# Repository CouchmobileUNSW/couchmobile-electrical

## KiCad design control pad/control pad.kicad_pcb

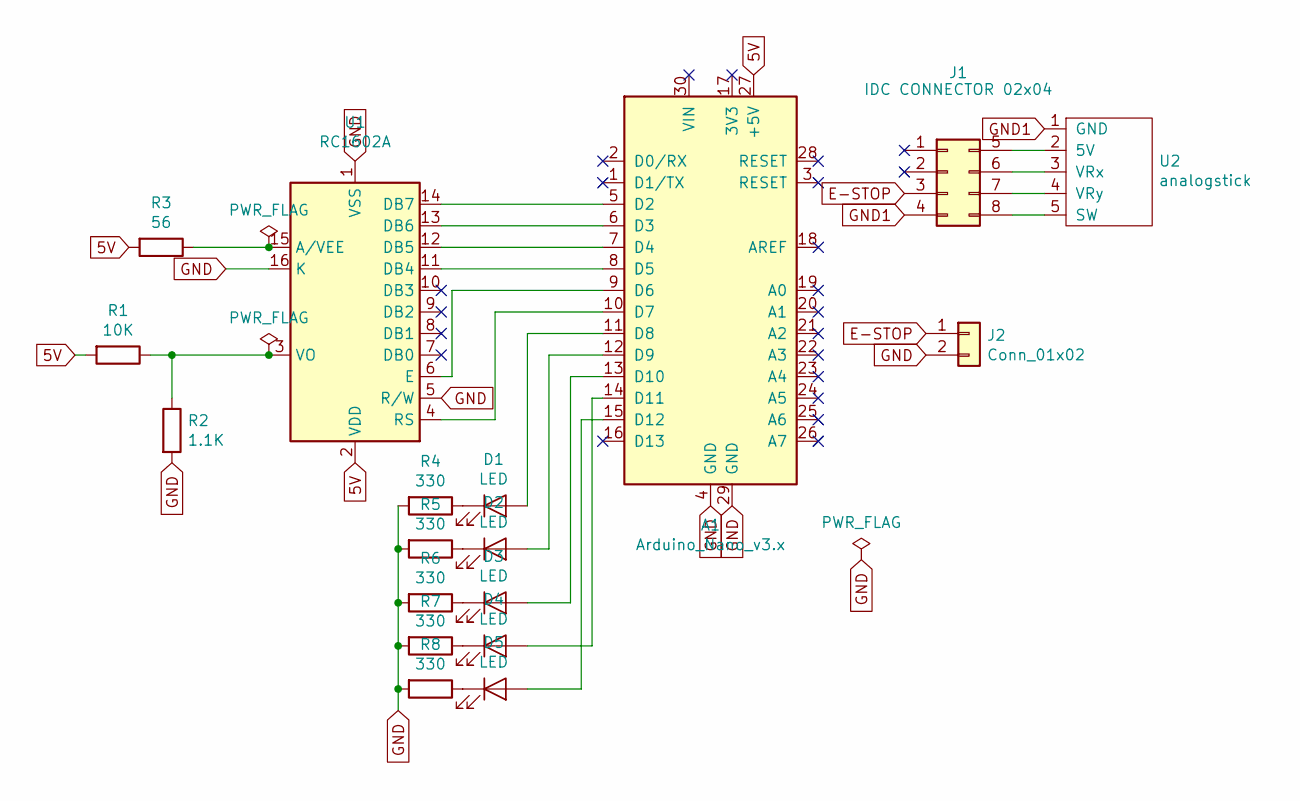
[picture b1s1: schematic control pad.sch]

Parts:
A1: Arduino_Nano_v3.x; Arduino_Nano_WithMountingHoles
D1, D2, D3, D4, D5: LED; D_0805_2012Metric_Pad1.15x1.40mm_HandSolder
J1: IDC CONNECTOR 02x04; IDC-Header_2x04_P2.54mm_Vertical
J2: Conn_01x02; PinHeader_1x02_P2.54mm_Vertical
R1: 10K; R_0805_2012Metric_Pad1.15x1.40mm_HandSolder
R2: 1.1K; R_0805_2012Metric_Pad1.15x1.40mm_HandSolder
R3: 56; R_0805_2012Metric_Pad1.15x1.40mm_HandSolder
R4, R5, R6, R7, R8: 330; R_0805_2012Metric_Pad1.15x1.40mm_HandSolder
U1: RC1602A; WC1602A
U2: analogstick; PinHeader_1x05_P2.54mm_Vertical

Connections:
5V: A1.27 (+5V), R1.2, R3.2, U1.2 (VDD)
E-STOP: J1.3, J2.1
GND: A1.4 (GND), A1.29 (GND), J2.2, R2.2, R4.2, R5.2, R6.2, R7.2, R8.2, U1.1 (VSS), U1.5 (R/W), U1.16 (K)
GND1: J1.4, U2.1 (GND)
unnamed: A1.5 (D2), U1.14 (DB7)
unnamed: A1.6 (D3), U1.13 (DB6)
unnamed: A1.7 (D4), U1.12 (DB5)
unnamed: A1.8 (D5), U1.11 (DB4)
unnamed: A1.9 (D6), U1.6 (E)
unnamed: A1.10 (D7), U1.4 (RS)
unnamed: A1.11 (D8), D1.2 (A)
unnamed: A1.12 (D9), D2.2 (A)
unnamed: A1.13 (D10), D3.2 (A)
unnamed: A1.14 (D11), D4.2 (A)
unnamed: A1.15 (D12), D5.2 (A)
unnamed: D1.1 (K), R4.1
unnamed: D2.1 (K), R5.1
unnamed: D3.1 (K), R6.1
unnamed: D4.1 (K), R7.1
unnamed: D5.1 (K), R8.1
unnamed: J1.5, U2.2 (5V)
unnamed: J1.6, U2.3 (VRx)
unnamed: J1.7, U2.4 (VRy)
unnamed: J1.8, U2.5 (SW)
unnamed: R1.1, R2.1, U1.3 (VO)
unnamed: R3.1, U1.15 (A/VEE)

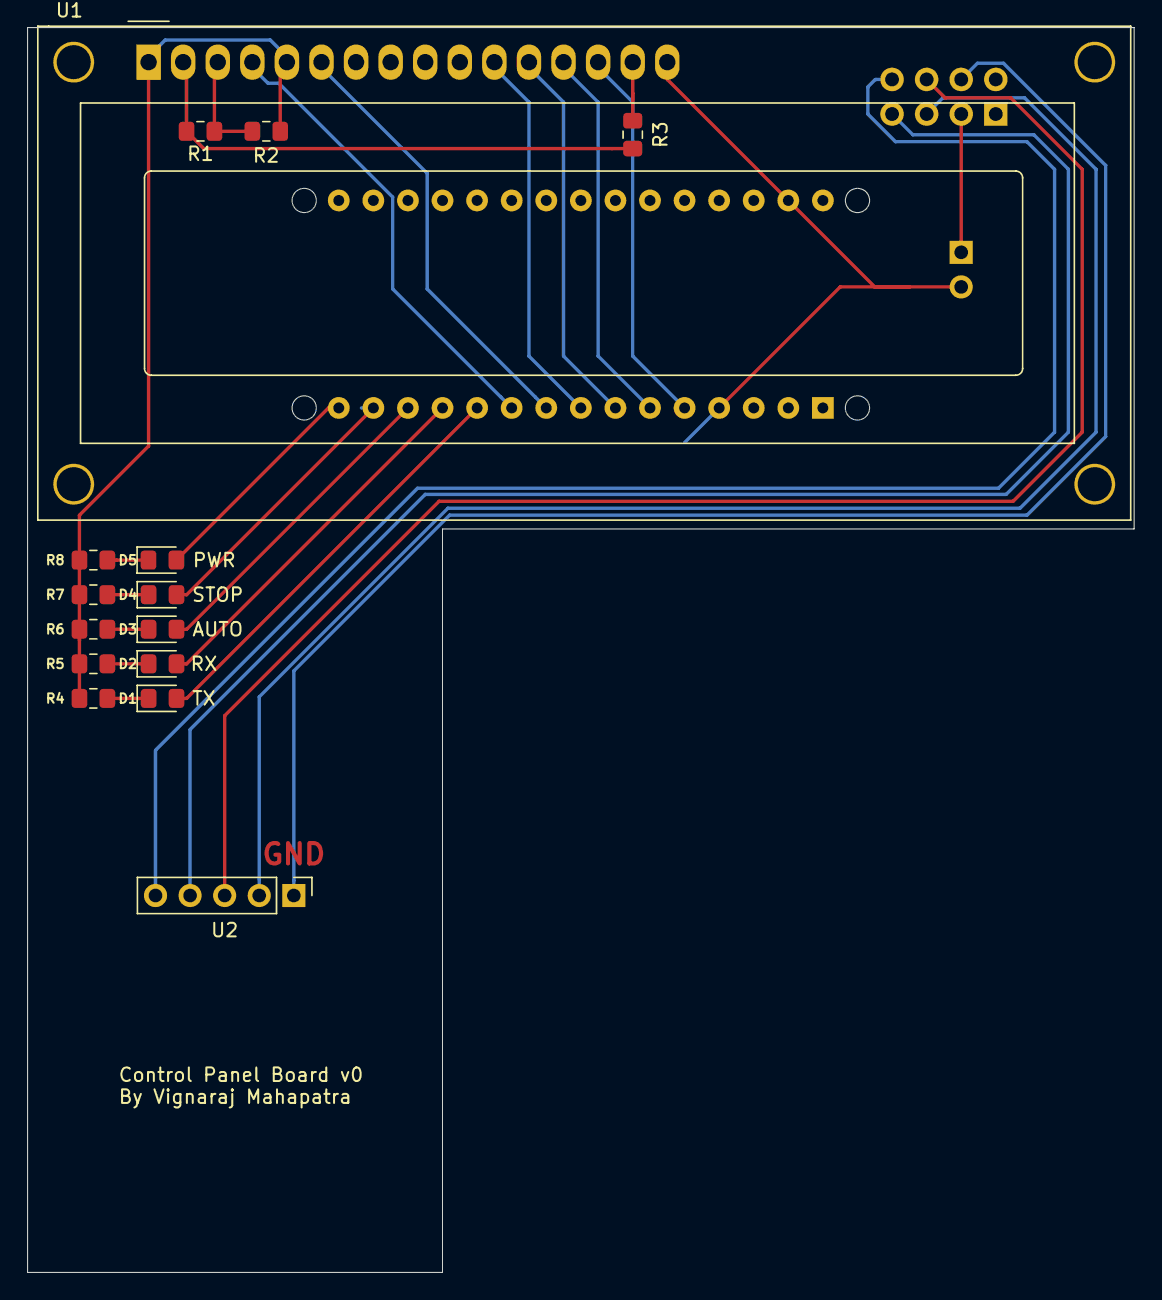
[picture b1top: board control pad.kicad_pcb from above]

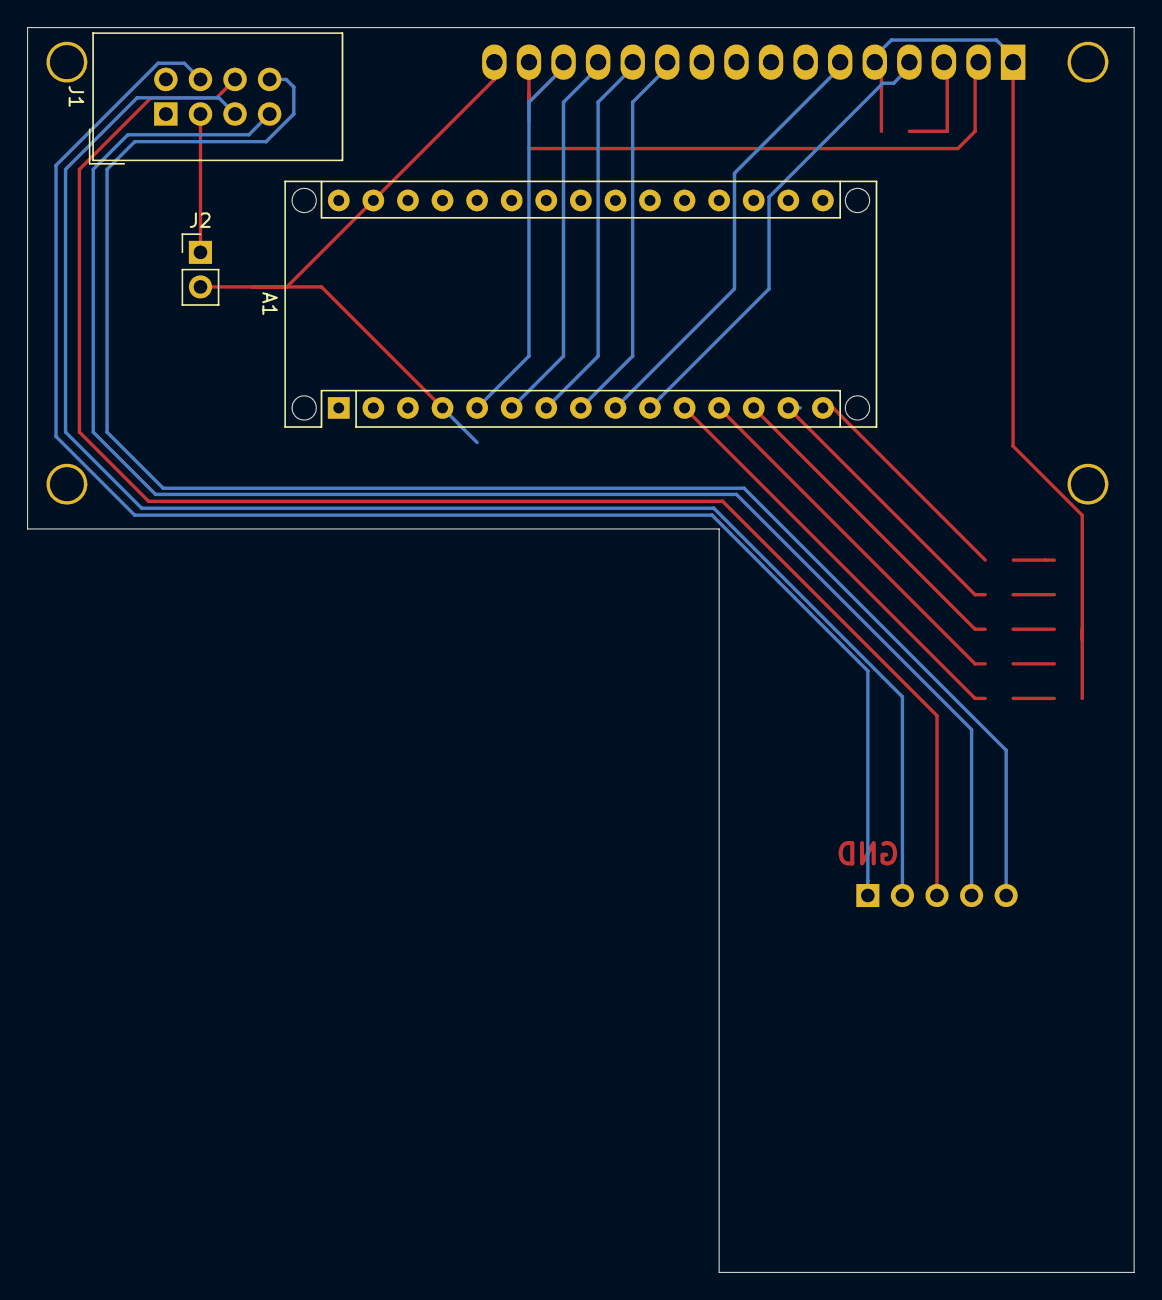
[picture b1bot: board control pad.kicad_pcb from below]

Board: 2 copper layers, 81.3 x 91.4 mm, 18 parts (3 on the bottom side), 26 nets.

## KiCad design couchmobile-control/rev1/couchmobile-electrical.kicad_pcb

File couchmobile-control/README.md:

TODO for Rev1:

Changes:
MISO, MOSI, SCK need to be made 5V tolerant, or removed (DONE)
BNO080 footprint needs to be widened by 2.54mm (DONE)
Traces under RF module should be adjusted slightly so they spend less time under the RF module (DONE)
Resistor and LED designators for status LEDs should be swapped around in position; ie the LED designator should be facing towards the outside (SKIPPED; no need)
SO-8 footprint needs to be made smaller (DONE)
HC74 DIP 14 needs to be made bigger (SKIPPED)
E_ON should be inverted signal of the signal sent to the HC74 AND gate (DONE)
Change to IDC 02x04 connector for connection to control panel (DONE)
Add silkscreen labels to pinouts (DONE)

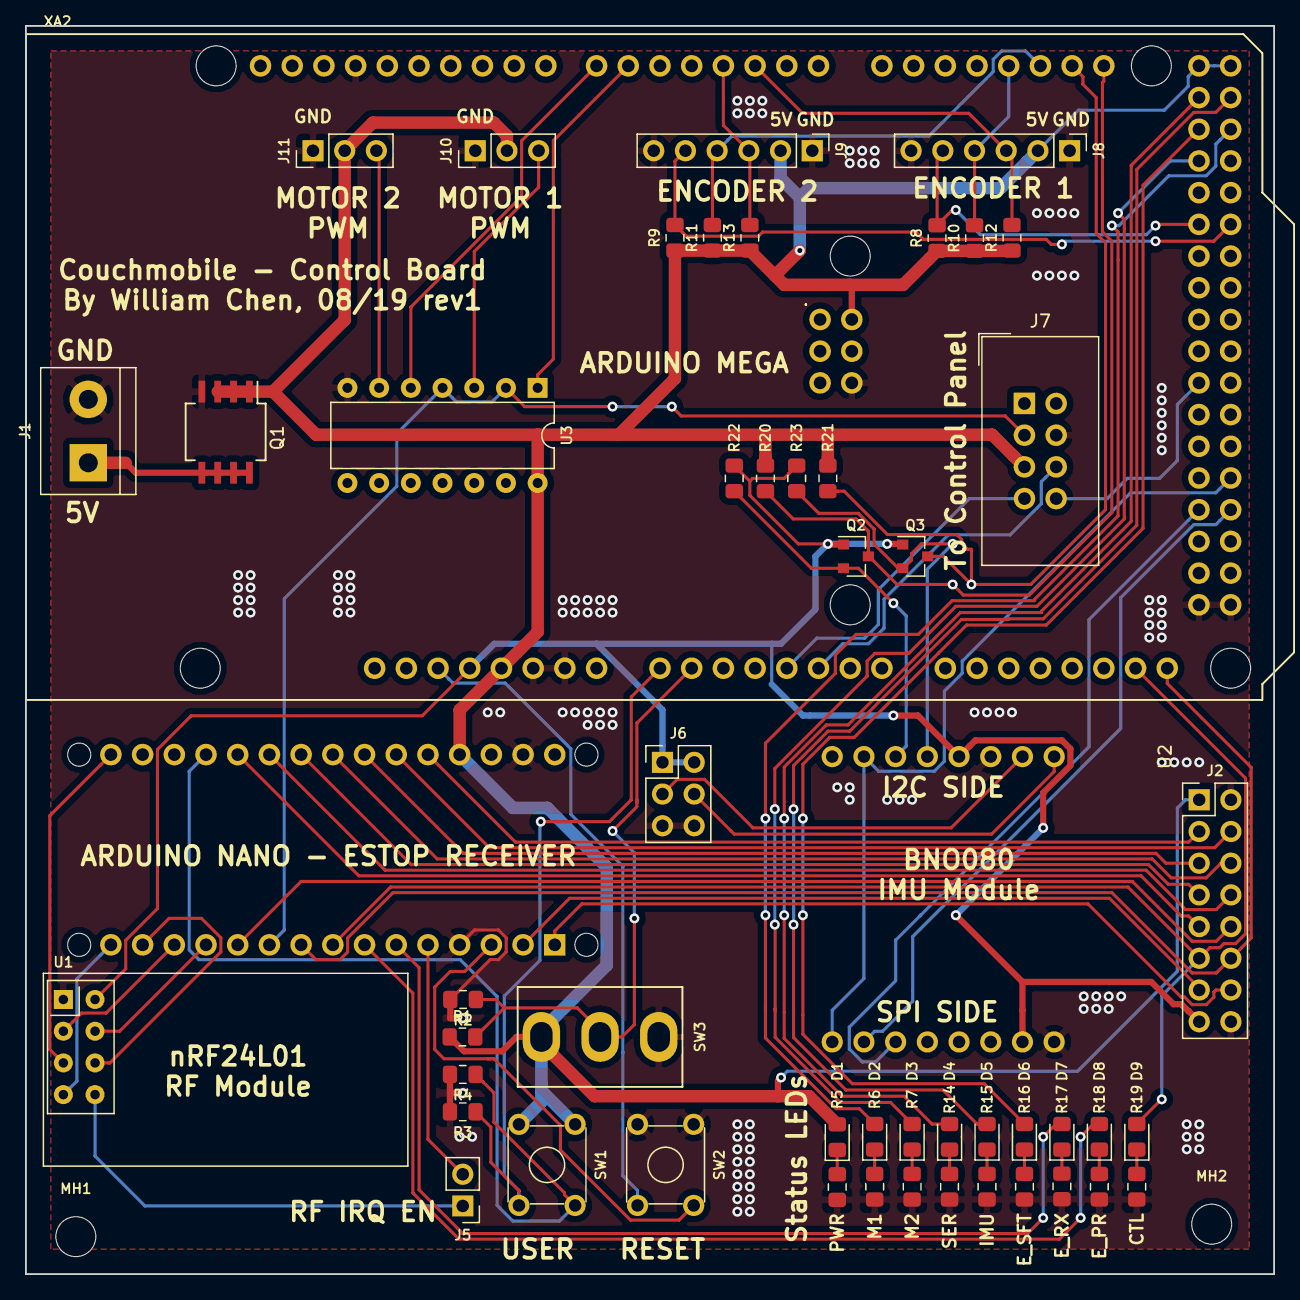
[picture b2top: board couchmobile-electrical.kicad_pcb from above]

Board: 2 copper layers, 100.0 x 100.0 mm, 54 parts (1 on the bottom side), 67 nets.

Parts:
D1: STATUS_PWR; LED_0805_2012Metric_Pad1.15x1.40mm_HandSolder
D2: STATUS_M1; LED_0805_2012Metric_Pad1.15x1.40mm_HandSolder
D3: STATUS_M2; LED_0805_2012Metric_Pad1.15x1.40mm_HandSolder
D4: STATUS_SERIAL; LED_0805_2012Metric_Pad1.15x1.40mm_HandSolder
D5: STATUS_IMU; LED_0805_2012Metric_Pad1.15x1.40mm_HandSolder
D6: STATUS_ENCODER; LED_0805_2012Metric_Pad1.15x1.40mm_HandSolder
D7: ESTOP_RX; LED_0805_2012Metric_Pad1.15x1.40mm_HandSolder
D8: ESTOP_EN; LED_0805_2012Metric_Pad1.15x1.40mm_HandSolder
D9: ESTOP_ON; LED_0805_2012Metric_Pad1.15x1.40mm_HandSolder
J1: Power_In; TerminalBlock_bornier-2_P5.08mm
J2: GPIO_NANO_1; PinHeader_2x08_P2.54mm_Vertical
J5: ESTOP_IRQ_EN; PinHeader_1x02_P2.54mm_Vertical
J6: BNO_COMM_CTRL; PinHeader_2x03_P2.54mm_Vertical
J7: Conn_02x04_Top_Bottom; IDC-Header_2x04_P2.54mm_Vertical
J8: Encoder1; PinHeader_1x06_P2.54mm_Vertical
J9: Encoder2; PinHeader_1x06_P2.54mm_Vertical
J10: Motor1; PinHeader_1x03_P2.54mm_Vertical
J11: Motor2; PinHeader_1x03_P2.54mm_Vertical
MH1, MH2: MountingHole; MountingHole_3.2mm_M3_ISO7380
Q1: PMOS DGS; SO-8_DGS
Q2, Q3: BSS138; SOT-23
R1, R2, R3, R4, R20, R21, R22, R23: 10k; R_0805_2012Metric_Pad1.15x1.40mm_HandSolder
R5, R6, R7, R8, R9, R10, R11, R12, R13, R14, R15, R16, R17, R18, R19: 2.2k; R_0805_2012Metric_Pad1.15x1.40mm_HandSolder
SW1: User Button; SW_TH_Tactile_Omron_B3F-10xx
SW2: RESET; SW_TH_Tactile_Omron_B3F-10xx
SW3: User Switch; MTS_3_pin_toggle_switch
U1: NRF24L01_Breakout; nRF24L01_Breakout
U2: BNO080
U3: 74LS08; DIP-14_W7.62mm
XA1: Arduino_Nano_Socket
XA2: Arduino_Mega2560_Shield

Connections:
+3V3: J2.15, J6.1, J6.2, Q2.1, Q3.1, R22.2, R23.2, U1.2, U2.3, U2.9, XA2.3V3
+5V: D1.2, J2.1, J7.5, J8.2, J9.2, J10.2, J11.2, Q1.3, R1.1, R8.1, R9.1, R10.1, R11.1, R12.1, R13.1, R20.1, R21.1, SW1.1, SW1.3, SW3.3, U3.14, XA1.5V, XA2.5V1, XA2.5V2, XA2.5V3, XA2.5V4
/EN1_1: J8.3, R12.2, XA2.D2
/EN1_2: J8.4, R10.2, XA2.D18
/EN1_3: J8.5, R8.2, XA2.D30
/EN2_1: J9.3, R13.2, XA2.D3
/EN2_2: J9.4, R11.2, XA2.D19
/EN2_3: J9.5, R9.2, XA2.D31
/ESTOP_CE: U1.3, XA1.D10
/ESTOP_CSN: U1.4, XA1.D9
/ESTOP_EN: D8.2, XA1.D4
/ESTOP_HS: J2.12, XA1.D6, XA2.A15
/ESTOP_IRQ: J5.1, U1.8
/ESTOP_MISO: U1.7, XA1.D12
/ESTOP_MOSI: U1.6, XA1.D11
/ESTOP_ON: D9.2, J2.11, XA1.D5, XA2.A14
/ESTOP_RX: D7.2, XA1.D3
/ESTOP_SCK: U1.5, XA1.D13
/ESTOP_TRAN: J7.3, U3.2, U3.4, XA1.D7
/IMU_CS: U2.13, XA2.D48
/IMU_RESET: U2.6, U2.15, XA2.D47
/IMU_WAKE: U2.14, XA2.D49
/JOYSTICK_SW: J7.8, XA2.D40
/JOYSTICK_X: J7.6, XA2.A5
/JOYSTICK_Y: J7.7, XA2.A4
/M1_OUT: J10.3, U3.3
/M2_OUT: J11.3, U3.6
/MEGA_RESET: SW2.4, XA2.RST1
/MEGA_SW1: R3.1, SW1.4, XA2.A0
/MEGA_SW2: R1.2, R2.1, SW3.2, XA2.A1
/NANO_A1: J2.9, XA1.A1
/NANO_A2: J2.8, XA1.A2
/NANO_A3: J2.7, XA1.A3
/NANO_A4: J2.6, XA1.A4
/NANO_A5: J2.5, XA1.A5
/NANO_A6: J2.4, XA1.A6
/NANO_A7: J2.3, XA1.A7
/NANO_D8: J2.10, XA1.D8
/NANO_INT0: J5.2, XA1.D2
/NANO_RESET: SW2.2, XA1.RST1
/NANO_RX: J2.13, XA1.D0
/NANO_SW1: R4.1, SW1.2, XA1.A0
/NANO_TX: J2.14, XA1.D1
/PWM_M1: U3.1, XA2.D6
/PWM_M2: U3.5, XA2.D7
/SCL: Q2.3, R20.2, XA2.D21
/SCL_3V3: Q2.2, R22.1, U2.5
/SDA: Q3.3, R21.2, XA2.D20
/SDA_3V3: Q3.2, R23.1, U2.4
/STATUS_ENC: D6.2, XA2.D24
/STATUS_IMU: D5.2, XA2.D23
/STATUS_M1: D2.2, XA2.D25
/STATUS_M2: D3.2, XA2.D26
/STATUS_SERIAL: D4.2, XA2.D22
GND: J1.2, J2.2, J2.16, J6.5, J6.6, J7.4, J8.1, J8.6, J9.1, J9.6, J10.1, J11.1, Q1.2, R2.2, R3.2, R4.2, R5.2, R6.2, R7.2, R14.2, R15.2, R16.2, R17.2, R18.2, R19.2, SW2.1, SW2.3, SW3.1, U1.1, U2.2, U2.8, U3.7, XA1.GND1, XA1.GND2, XA2.GND1, XA2.GND2, XA2.GND3, XA2.GND4, XA2.GND5, XA2.GND6
unnamed: D1.1, R5.1
unnamed: D2.1, R6.1
unnamed: D3.1, R7.1
unnamed: D4.1, R14.1
unnamed: D5.1, R15.1
unnamed: D6.1, R16.1
unnamed: D7.1, R17.1
unnamed: D8.1, R18.1
unnamed: D9.1, R19.1
unnamed: J1.1, Q1.1
unnamed: J6.3, U2.1
unnamed: J6.4, U2.0

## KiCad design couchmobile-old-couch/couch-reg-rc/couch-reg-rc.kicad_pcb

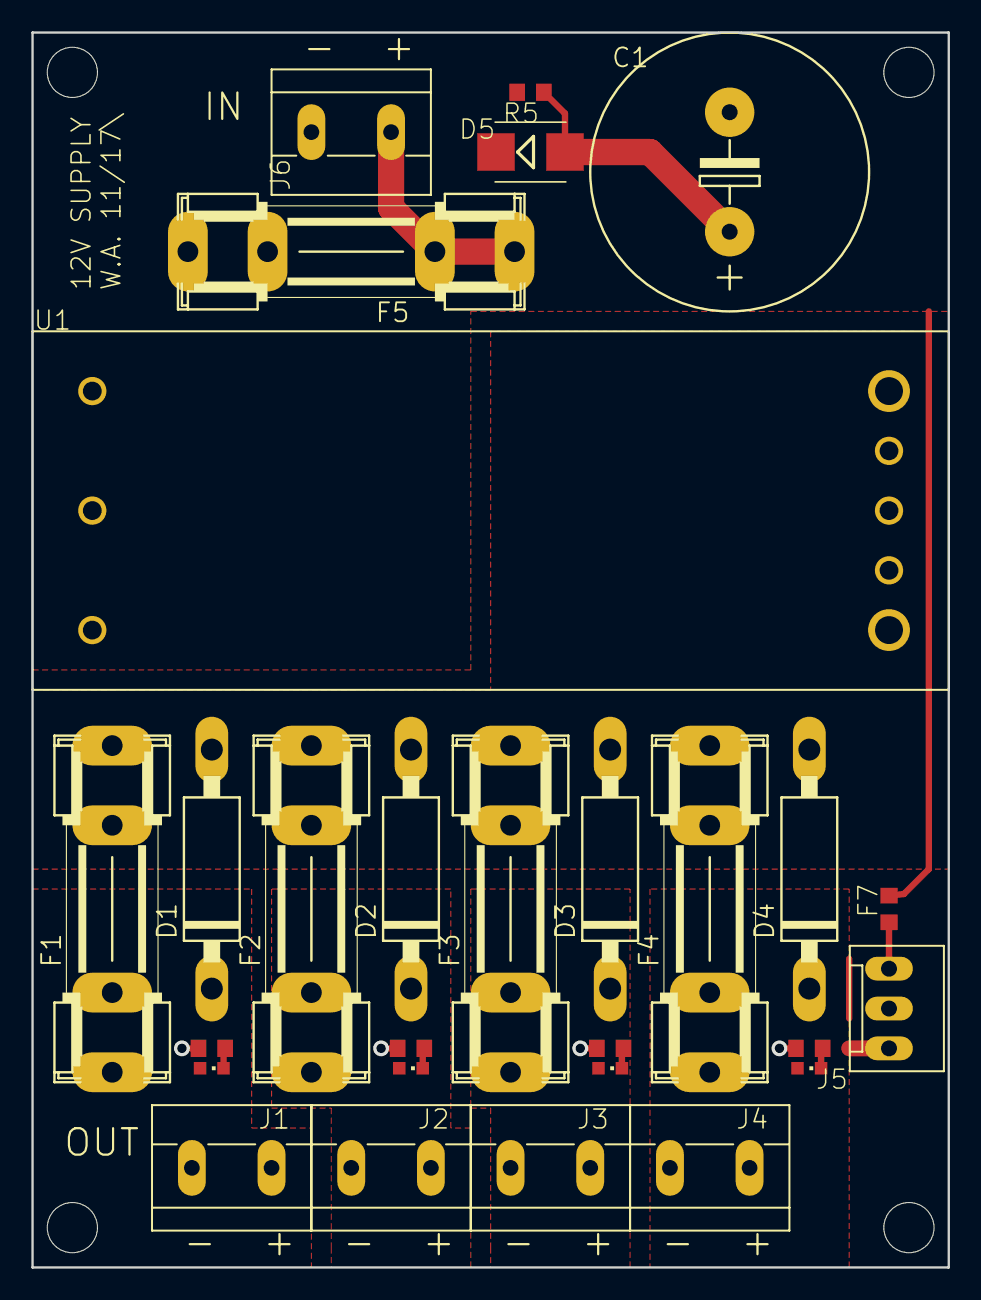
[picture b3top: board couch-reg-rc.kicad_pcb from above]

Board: 2 copper layers, 58.4 x 78.7 mm, 32 parts (0 on the bottom side), 15 nets.

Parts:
@HOLE0, @HOLE1, @HOLE2, @HOLE3: (no value)
C1: 1200uF, 80V; E7,5-18
D1, D2, D3, D4: 16V; C1702-15
D5: DIODE-SMB; SMB
F1: 6.3A; SHK20L
F2, F3, F4: 2A; SHK20L
F5: 4A; SHK20L
F7: 100mA; 0603
J1, J2, J3, J4, J6: PCBTERM2; PCBTERM
J5: MA03-1KK; MOLEX-3
LED1, LED2, LED3, LED4: LEDCHIPLED_0603; CHIPLED_0603
R1, R2, R3, R4: 5.6k; R0603
R5: 470; R0603
U1: E48SC12010

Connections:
+12V: F1.2A, F1.2B, F2.2A, F2.2B, F3.2A, F3.2B, F4.2A, F4.2B, U1.7, U1.8
GND: D1.A, D2.A, D3.A, D4.A, J1.2, J2.2, J3.2, J4.2, J5.2, R1.1, R2.1, R3.1, R4.1, U1.4, U1.5
unnamed: C1.+, D5.A, R5.1
unnamed: D1.C, F1.1A, F1.1B, J1.1, LED1.A
unnamed: D2.C, F2.1A, F2.1B, J2.1, LED2.A
unnamed: D3.C, F3.1A, F3.1B, J3.1, LED3.A
unnamed: D4.C, F4.1A, F4.1B, J4.1, J5.3, LED4.A
unnamed: F5.1A, F5.1B, J6.2
unnamed: F7.1, J5.1
unnamed: LED1.C, R1.2
unnamed: LED2.C, R2.2
unnamed: LED3.C, R3.2
unnamed: LED4.C, R4.2
PE: C1.-, J6.1, U1.3
V+: D5.C, F5.2A, F5.2B, F7.2, R5.2, U1.1

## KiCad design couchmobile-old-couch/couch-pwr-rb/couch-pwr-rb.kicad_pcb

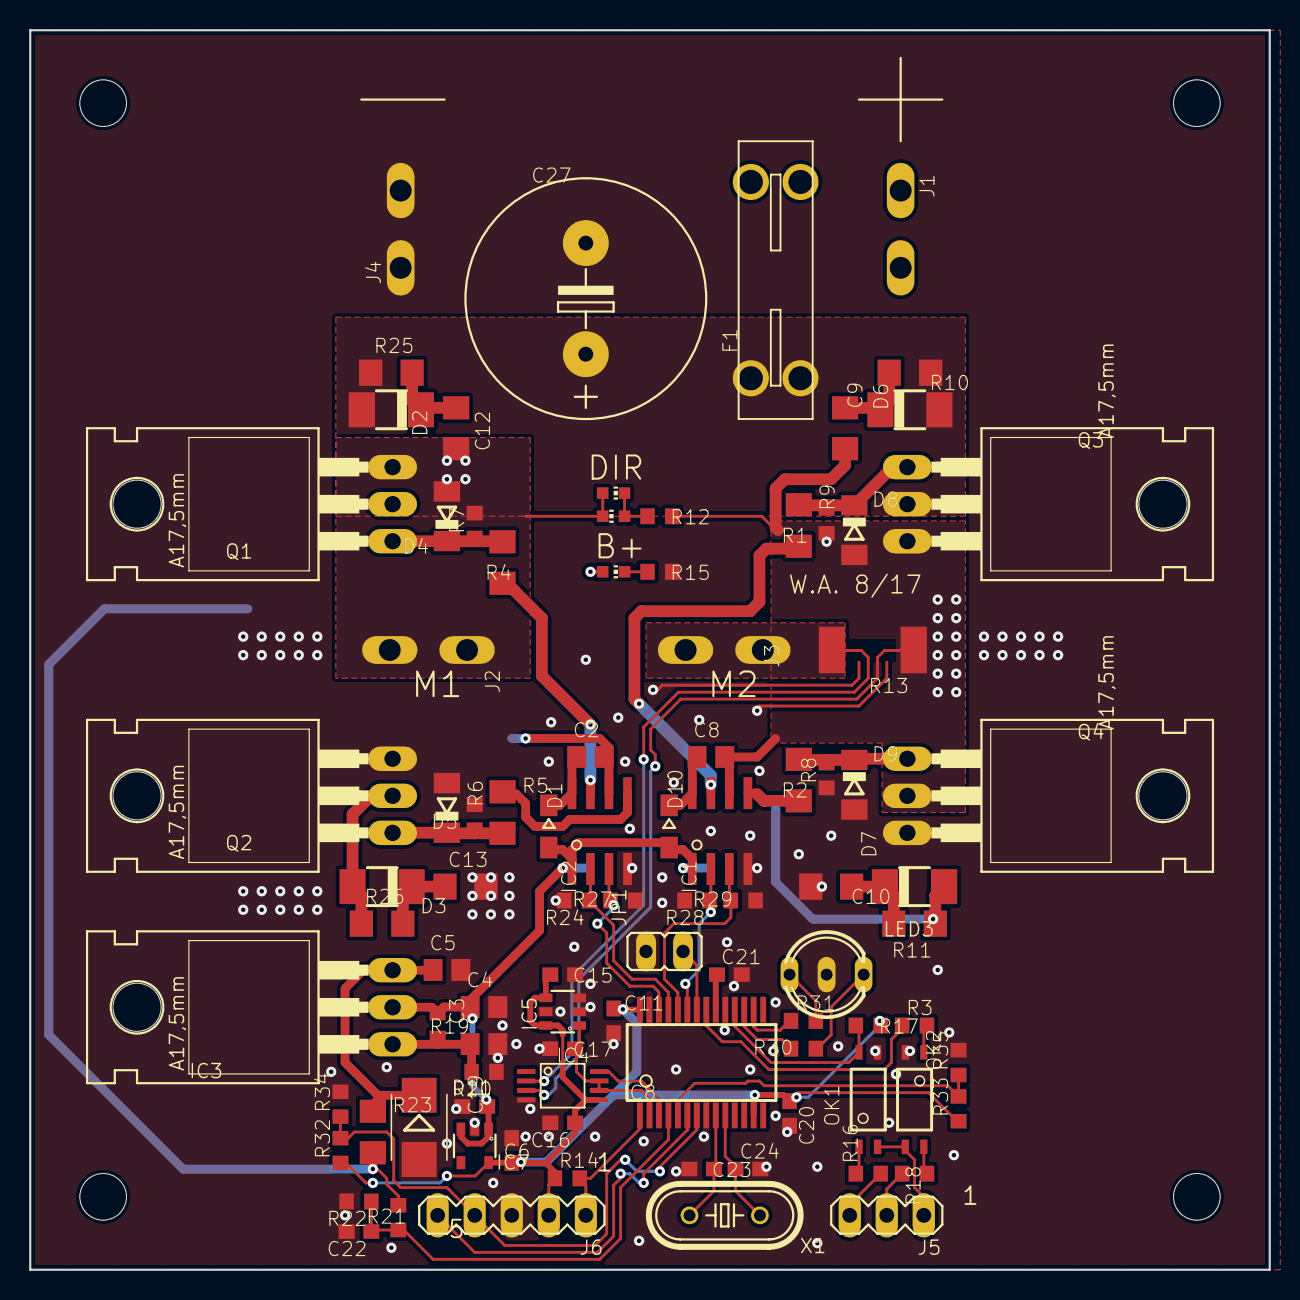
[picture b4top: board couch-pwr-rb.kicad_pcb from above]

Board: 2 copper layers, 85.0 x 85.0 mm, 110 parts (0 on the bottom side), 53 nets.

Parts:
@HOLE0, @HOLE1, @HOLE2, @HOLE3: (no value)
C1, C2, C3, C4, C7, C8: 1uF; C0805
C5: 100nF; C0805
C6, C19: 1uF; C0603
C9, C10, C12, C13: 1nF, 100V; C1206
C11, C15, C16, C20, C22: 100nF; C0603
C14: 4.7uF GRM32ER71K475KE14L; C1210
C17: DNP; C0603
C18: 4.7uF; C1210
C21: 10uF; C0603
C23, C24: 18pF; C0603
C25, C26: 100nF; C1206
C27: 470uF; E7,5-16
D1, D10: DIODE-SOD323-W; SOD323-W
D2, D3, D6, D7: DNP; DO-214AC
D4, D5, D8, D9: 15V; SOD80C
D11: 56V; SMB
D12, D13, D14, D15: DNP; SMC
F1: 30A; BLADEFUSE
IC1, IC2: IRS21867; SO-08
IC3: LM317TLBH; TO220BH
IC4: INA240; VSSOP-8
IC5: MCP1501-CHY; SOT23-6
IC7: AP2204K-3.3; SOT23-5
IC8: DSPIC33EPMC202-SS; SSOP-28
J1, J2, J3, J4: PIN262409-1; 62409-1
J5: MA03-1
J6: MA05-1
JP1: JP1E; JP1
LED1, LED2, LED5: LEDCHIP-LED0603; CHIP-LED0603
LED3: DUOLED-RG-C; DUOLED-C-5MM
OK1, OK2: VOS617A; MINI-FLAT-4
Q1, Q2, Q3, Q4: PMOSFET_NTO220BH; TO220BH
R1, R2, R4, R5: 6.8; R1206
R3, R16, R19: 270; R0603
R6, R7, R8, R9: 2.7k; R0603
R10, R11, R25, R26: 2.2; R1206
R12, R15: 27k; R0603
R13: 1m; R2512
R14, R32, R33: 10k; R0603
R17: 2k; R0603
R18: 75; R0603
R20: 2.2k; R0603
R21: 82k; R0603
R22: 3.3k; R0603
R23: 47; R1206
R24, R27, R28, R29: 1k; R0603
R30, R31: 680; R0603
R34, R35: NTC 10k; R0603
TV1, TV2, TV3: TVS-UNI; SMC
X1: 16MHz; HC49_S

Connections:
+3V3: C6.1, C11.1, C15.2, C16.1, C20.1, IC4.P5, IC5.4, IC5.6, IC7.5, IC8.13, IC8.28, J6.2, R14.1, R17.1, R32.1, R33.1
+12V: C1.1, C4.1, C7.1, C19.1, D1.A, D10.A, IC1.1, IC2.1, IC3.D, IC7.1, IC7.3, R19.2
/ISNS: IC4.P8, IC8.3
/PGC: IC8.6, J6.5
/PGD: IC8.7, J6.4, R32.2, R34.1
/RCIN: IC8.18, OK1.4, R17.2
/RCOUT: IC8.21, R3.1
/TH1: IC8.5, R33.2, R35.1
/VREF: C17.1, IC4.P6, IC4.P7, IC5.1, IC8.2
/VSNS: C22.1, IC8.4, R21.2, R22.1
/~MCLR: IC8.1, J6.1, R14.2
unnamed: C2.1, D1.C, IC2.8
unnamed: C3.1, IC3.G, R19.1, R20.2
unnamed: C5.1, D11.C, IC3.S, R23.1
unnamed: C8.1, D10.C, IC1.8
unnamed: C8.2, C9.2, D7.A, D8.A, D14.A, D15.C, IC1.6, IC4.P3, Q3.S, Q4.D, R9.2, R11.1, R12.1, R13.1, TV2.1
unnamed: C9.1, D6.C, R10.2
unnamed: C10.1, D7.C, R11.2
unnamed: C12.1, D2.C, R25.2
unnamed: C2.2, C12.2, D3.A, D4.A, D12.A, D13.C, IC2.6, J2.A1, J2.A2, LED1.A, LED2.C, Q1.S, Q2.D, R7.2, R26.1, TV3.1
unnamed: C13.1, D3.C, R26.2
unnamed: C21.1, IC8.20
unnamed: C23.1, IC8.9, X1.2
unnamed: C24.1, IC8.10, X1.1
unnamed: D4.C, Q1.G, R4.2, R7.1
unnamed: D5.C, Q2.G, R5.2, R6.2
unnamed: D8.C, Q3.G, R1.2, R9.1
unnamed: D9.C, Q4.G, R2.2, R8.2
unnamed: F1.2A, F1.2B, J1.A1, J1.A2
unnamed: IC1.2, IC8.23, R28.1
unnamed: IC1.3, IC8.24, R29.1
unnamed: IC1.5, R2.1
unnamed: IC1.7, R1.1
unnamed: IC2.2, IC8.25, R24.1
unnamed: IC2.3, IC8.26, R27.1
unnamed: IC2.5, R5.1
unnamed: IC2.7, R4.1
unnamed: IC4.P2, J3.A1, J3.A2, R13.2
unnamed: IC8.16, R31.1
unnamed: IC8.17, R30.1
unnamed: IC8.22, JP1.2
unnamed: J5.1, OK1.2, OK2.3
unnamed: J5.2, R18.1
unnamed: J5.3, R16.2
unnamed: LED1.C, LED2.A, R12.2
unnamed: LED3.AR, R30.2
unnamed: LED3.AX, R31.2
unnamed: LED5.C, R15.2
unnamed: OK1.1, R16.1
unnamed: OK2.1, R3.2
unnamed: OK2.4, R18.2
PE: C1.2, C3.2, C4.2, C5.2, C6.2, C7.2, C10.2, C11.2, C13.2, C14.2, C15.1, C16.2, C17.2, C18.2, C19.2, C20.2, C21.2, C22.2, C23.2, C24.2, C25.2, C26.2, C27.-, D5.A, D9.A, D11.A, D13.A, D15.A, IC1.4, IC2.4, IC4.P4, IC5.2, IC5.3, IC5.5, IC7.2, IC8.8, IC8.19, IC8.27, J4.A1, J4.A2, J6.3, JP1.1, LED3.C, OK1.3, OK2.2, Q2.S, Q4.S, R6.1, R8.1, R15.1, R20.1, R22.2, R24.2, R27.2, R28.2, R29.2, R34.2, R35.2, TV1.2, TV2.2, TV3.2
V+: C14.1, C18.1, C25.1, C26.1, C27.+, D2.A, D6.A, D12.C, D14.C, F1.1A, F1.1B, LED5.A, Q1.D, Q3.D, R10.1, R21.1, R23.2, R25.1, TV1.1

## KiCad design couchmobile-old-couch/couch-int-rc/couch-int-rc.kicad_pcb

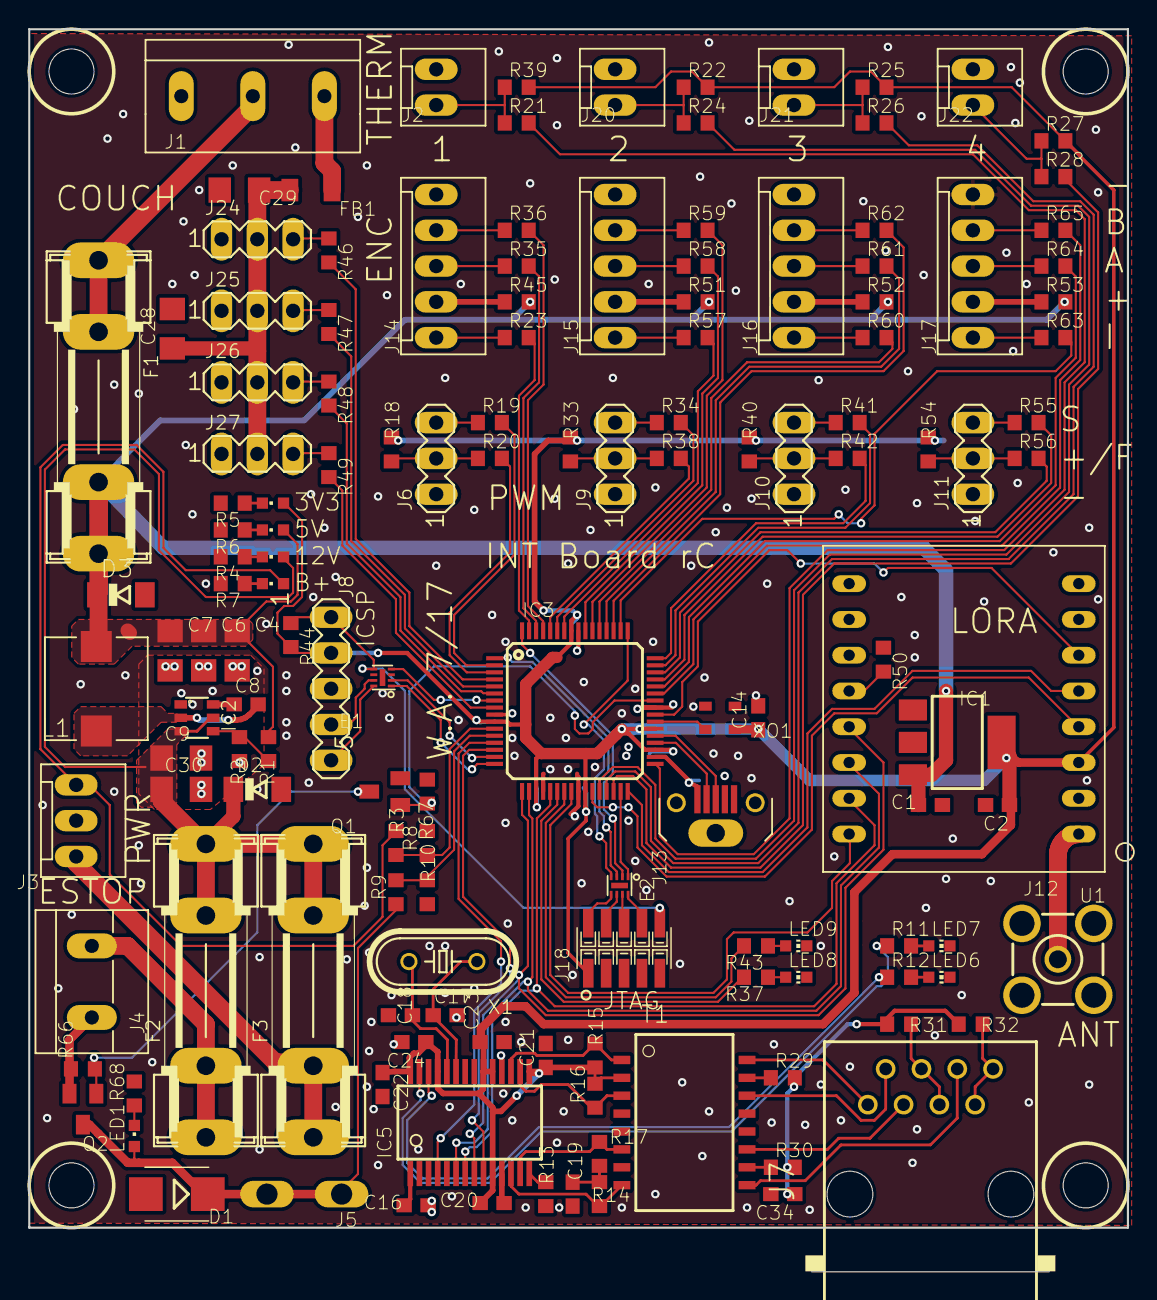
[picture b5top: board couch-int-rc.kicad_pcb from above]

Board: 2 copper layers, 78.0 x 88.2 mm, 154 parts (0 on the bottom side), 131 nets.

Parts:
@HOLE0, @HOLE1, @HOLE2, @HOLE3: (no value)
C1, C2, C25: 1uF; C0603
C3, C5, C8, C10, C11, C12, C13, C14, C19, C20, C21, C22, C23, C24: 100nF; C0603
C4, C6, C7, C28, C29: 22uF; C1206
C9, C30: 10uF; C1206
C16: 10uF; C0603
C17, C18: 18pF; C0603
C34: 1nF; C0603
D1: DIODE-SMB; SMB
D2: 15V; SOD80C
D3: 5.6V; SOD80C
E1, E2: ESD4; WSON-8
F1: 2A; SHK20L
F2: 500mA; SHK20L
F3: 1A; SHK20L
FB1: L-USL3216C; L3216C
IC1: LD117A?S; SOT223
IC2: TPS56209; SOT23-6
IC3: PIC32MKMCF064; TQFP-64-10
IC5: ENC28J60SS; SSOP-28
J1: PCBTERM3
J2, J20, J21, J22: MA02-1; MOLEX-2
J3: MA03-1KK; MOLEX-3
J4: PCBTERM2; PCBTERM
J5: PIN262409-1; 62409-1
J6, J9, J10, J11, J24, J25, J26, J27: MA03-1
J7: RJ45; RJ45-NO-SHIELD
J8: MA05-1
J12: BU-SMA-V
J13: USB-MICROB1051330001; 1051330001
J14, J15, J16, J17: MA05-1; MOLEX-5
J18: 1296-T10; 1296-10
L1: Farnell 1864471; MCSDRH73B
LED1: ESTOP; CHIPLED_0603
LED2: 3.3V rail; CHIPLED_0603
LED3: 5V rail; CHIPLED_0603
LED4: 12V rail; CHIPLED_0603
LED5: Motor power; CHIPLED_0603
LED6, LED7, LED8, LED9: LEDCHIP-LED0603; CHIP-LED0603
Q1: BSS123; SOT23
Q2: DMP3099L; SOT23
R1: 56k; R0603
R2, R66, R67: 10k; R0603
R3: 82k; R0603
R4, R68: 5.6k; R0603
R5, R37, R43: 680; R0603
R6: 1.5k; R0603
R7: 27k; R0603
R8: 3.3k; R0603
R9: 33k; R0603
R10: 6.8k; R0603
R11, R12, R18, R33, R40, R54: 330; R0603
R13: 2k; R0603
R14, R15, R16, R17: 49.9; R0603
R19, R20, R21, R23, R24, R26, R28, R34, R35, R36, R38, R41, R42, R46, R47, R48, R49, R55, R56, R57, R58, R59, R60, R61, R62, R63, R64, R65: 470; R0603
R22, R25, R27, R39, R44, R50: 4.7k; R0603
R29, R30, R31, R32: 75; R0603
R45, R51, R52, R53: PTC4.7; R0603
T1: TG110-EN5; N5
U1: RF-LORA-PD; RF-LORA-DIP
X1: 25MHz; HC49_S
XO1: ASE

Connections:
+3V3: C2.1, C3.1, C5.1, C10.1, C11.1, C12.1, C13.1, C14.1, C20.1, C21.1, C22.1, C23.1, C24.1, IC1.4, IC3.10, IC3.19, IC3.26, IC3.35, IC3.38, IC3.57, IC5.10, IC5.15, IC5.19, IC5.20, IC5.25, IC5.28, J8.2, J18.1, LED2.A, R15.2, R16.2, R18.1, R22.2, R25.2, R27.2, R33.1, R39.2, R40.1, R44.2, R54.1, T1.2, U1.P$3, XO1.4
+5V: C1.1, C4.1, C6.1, C7.1, D3.C, F1.2A, F1.2B, IC1.3, L1.P$2, LED3.A, R1.2, R45.2, R51.2, R52.2, R53.2
+12V: C9.1, C30.1, D2.C, F2.2A, F2.2B, F3.2A, F3.2B, IC2.3, IC2.5, LED4.A
/couch-int-rc_3/PGC: E1.1, IC3.16
/couch-int-rc_3/PGD: E1.2, IC3.15
/couch-int-rc_3/RX_DONE: IC3.40, U1.P$6
/couch-int-rc_3/RX_SW: IC3.27, U1.P$4
/couch-int-rc_3/STAT1: IC3.22, R37.2
/couch-int-rc_3/STAT2: IC3.23, R43.2
/couch-int-rc_3/TCK: E2.3, IC3.1
/couch-int-rc_3/TCKI: E2.6, J18.4
/couch-int-rc_3/TDI: E2.1, IC3.31
/couch-int-rc_3/TDII: E2.8, J18.8
/couch-int-rc_3/TDO: E2.2, IC3.64
/couch-int-rc_3/TDOI: E2.7, J18.6
/couch-int-rc_3/TMS: E2.4, IC3.49
/couch-int-rc_3/TMSI: E2.5, J18.2
/couch-int-rc_3/TX_SW: IC3.32, U1.P$5
/couch-int-rc_3/~CS_L: IC3.24, U1.P$16
/couch-int-rc_3/~MCLR: E1.4, IC3.7
/couch-int-rc_3/~MCLRI: E1.5, J8.1, J18.10, R44.1
ESTOP_ENG: IC3.42, Q1.1, R67.1
ESTOP_SNS: IC3.12, R9.2, R10.1
GND: C1.2, C2.2, C3.2, C4.2, C5.2, C6.2, C7.2, C9.2, C10.2, C11.2, C12.2, C13.2, C14.2, C16.2, C17.2, C18.2, C19.2, C20.2, C21.2, C22.2, C23.2, C24.2, C25.2, C28.2, C29.2, C30.2, C34.2, D1.A, D2.A, D3.A, E1.9, E2.9, IC1.1, IC2.1, IC3.9, IC3.20, IC3.25, IC3.41, IC3.56, IC5.2, IC5.11, IC5.18, IC5.21, IC5.22, J1.1, J2.1, J3.2, J6.1, J8.3, J9.1, J10.1, J11.1, J12.2, J12.3, J12.4, J12.5, J13.5, J13.P$1, J13.P$2, J13.P$3, J18.3, J18.5, J18.9, J20.1, J21.1, J22.1, J24.1, J25.1, J26.1, J27.1, LED6.C, LED7.C, LED8.C, LED9.C, Q1.2, R2.1, R4.2, R5.2, R6.2, R7.2, R8.2, R10.2, R13.2, R50.1, R67.2, R68.2, U1.P$2, XO1.2
GPIO_0: IC3.4, R46.2
GPIO_1: IC3.5, R47.2
GPIO_2: IC3.6, R48.2
GPIO_3: IC3.8, R49.2
M1FB: IC3.3, R20.2
M1RC: IC3.2, R19.2
M2FB: IC3.60, R38.2
M2RC: IC3.59, R34.2
M3FB: IC3.48, R42.2
M3RC: IC3.47, R41.2
M4FB: IC3.46, R56.2
M4RC: IC3.45, R55.2
MISO: IC3.18, IC5.6, U1.P$14
MOSI: IC3.21, IC5.7, U1.P$15
unnamed: C8.1, IC2.6
unnamed: C8.2, IC2.2, L1.P$1
unnamed: C16.1, IC5.1
unnamed: C17.1, IC5.23, X1.1
unnamed: C18.1, IC5.24, X1.2
unnamed: C19.1, R14.2, R17.2
unnamed: C25.1, IC3.34, J13.1
unnamed: C28.1, C29.1, FB1.2, J24.2, J25.2, J26.2, J27.2
unnamed: C34.1, R29.2, R30.2, R31.2, R32.2
unnamed: D1.C, J5.A1, J5.A2, LED1.A, Q2.3, R9.1
unnamed: E1.7, J8.4
unnamed: E1.8, J8.5
unnamed: F1.1A, F1.1B, J1.2
unnamed: F2.1A, F2.1B, J4.2
unnamed: F3.1A, F3.1B, J3.3
unnamed: IC2.4, R1.1, R2.2
unnamed: IC3.36, J13.2
unnamed: IC3.37, J13.3
unnamed: IC3.39, XO1.3
unnamed: IC5.12, R14.1, T1.8
unnamed: IC5.13, R17.1, T1.6
unnamed: IC5.14, R13.1
unnamed: IC5.16, R16.1, T1.3
unnamed: IC5.17, R15.1, T1.1
unnamed: IC5.26, R12.1
unnamed: IC5.27, R11.1
unnamed: J2.2, R21.1, R39.1
unnamed: J4.1, Q2.2, R66.1
unnamed: J6.2, R18.2, R20.1
unnamed: J6.3, R19.1
unnamed: J7.1, T1.16
unnamed: J7.2, T1.14
unnamed: J7.3, T1.11
unnamed: J7.4, J7.5, R31.1
unnamed: J7.6, T1.9
unnamed: J7.7, J7.8, R32.1
unnamed: J9.2, R33.2, R38.1
unnamed: J9.3, R34.1
unnamed: J10.2, R40.2, R42.1
unnamed: J10.3, R41.1
unnamed: J11.2, R54.2, R56.1
unnamed: J11.3, R55.1
unnamed: J12.1, U1.P$1
unnamed: J14.4, R36.1
unnamed: J14.5, R35.1
unnamed: J15.4, R59.1
unnamed: J15.5, R58.1
unnamed: J16.4, R62.1
unnamed: J16.5, R61.1
unnamed: J17.4, R65.1
unnamed: J17.5, R64.1
unnamed: J20.2, R22.1, R24.1
unnamed: J21.2, R25.1, R26.1
unnamed: J22.2, R27.1, R28.1
unnamed: J24.3, R46.1
unnamed: J25.3, R47.1
unnamed: J26.3, R48.1
unnamed: J27.3, R49.1
unnamed: LED1.C, R68.1
unnamed: LED2.C, R5.1
unnamed: LED3.C, R6.1
unnamed: LED4.C, R4.1
unnamed: LED5.C, R7.1
unnamed: LED6.A, R12.2
unnamed: LED7.A, R11.2
unnamed: LED8.A, R37.1
unnamed: LED9.A, R43.1
unnamed: Q1.3, Q2.1, R66.2
unnamed: R29.1, T1.15
unnamed: R30.1, T1.10
unnamed: R50.2, U1.P$12
QEA_1: IC3.62, R35.2
QEA_2: IC3.55, R58.2
QEA_3: IC3.52, R61.2
QEA_4: IC3.44, R64.2
QEB_1: IC3.63, R23.2
QEB_2: IC3.58, R57.2
QEB_3: IC3.53, R60.2
QEB_4: IC3.50, R63.2
QEI_1: IC3.61, R36.2
QEI_2: IC3.54, R59.2
QEI_3: IC3.51, R62.2
QEI_4: IC3.43, R65.2
SCK: IC3.17, IC5.8, U1.P$13
TH1: IC3.33, R21.2
TH2: IC3.28, R24.2
TH3: IC3.29, R26.2
TH4: IC3.30, R28.2
V+: J3.1, LED5.A, R3.1
VBAT_SNS: IC3.11, R3.2, R8.1
VCCIO: FB1.1, J1.3
~CS_E: IC3.14, IC5.9
~INT_E: IC3.13, IC5.4

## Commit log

2019-08-04 First commit. Sending up almost finished schematic of control module.
2019-08-04 Finished nano gpio
2019-08-05 Finished wiring up schematic; DRC passed. ALso added in the AND gates
2019-08-05 Laid out the LEDs and switches
2019-08-06 Made and added so8 package for pfet
2019-08-06 Changed solder to mask clearance to 0.05mm. Wired up half the gpio for nano
2019-08-06 Wired up a lot of the busses.
2019-08-06 Added 5v to 3.3v line converters.
2019-08-07 Laid out most lines except ground
2019-08-07 Poured ground and did DRC. Fixed all markers.
2019-08-07 Changed some resistor values. Generated BOM.
2019-08-26 Finished rev1 of board
2019-08-26 Added in label to control panel
2019-08-27 Adding the couch control panel
2019-08-27 finished v0 of control pad pcb
2019-08-29 Updated labels on pcb revision 3
2019-09-22 Create LICENSE
